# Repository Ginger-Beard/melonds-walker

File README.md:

# melonDS-walker

A DIY USB-C dongle that lets Pokemon HeartGold/SoulSilver running in an emulator talk to a real Pokewalker. An ESP32-S3 and a Vishay TFBS4711 IrDA transceiver act as the IR link, with plug-and-play use after flashing.

This is a personal/community project, not a product. The goal is to upstream IR support into [melonDS Android](https://github.com/rafaelvcaetano/melonDS-android) (rafaelvcaetano/melonDS-android), or failing that to ship it in a fork.

## WARNING: destructive walker commands

Commands 0x2A and 0x2C make the walker wipe itself (pairing, walk, inventory, and for 0x2A lifetime steps), even though 0x2A also replies with the device ID. 0xF0 (factory setup), 0xFE (motion-test setup) and all write commands (EEPROM and RAM writes, walk start/end/update, gift and event commands) are also destructive. `walkerctl` never sends them: a hard-coded allowlist in its send path permits only 0xFA, 0x20, 0x24 and 0xF4 (plus 0x0C reads of exactly 3 payload bytes). Do not bypass this, and take care with any other tool pointed at a real walker.

## Status

Built, tested and working: as of 2026-11-17 the dongle is in regular use, playing HeartGold/SoulSilver in melonDS Android on an AYN Thor with a real Pokéwalker.

First hardware test, 2026-11-12: the XIAO IrDA hat v0.1 worked on first power-on with no rework, and the firmware with default settings talks to a real Pokéwalker. `tools/walkerctl.py handshake` succeeds, and `sniff`, `identify` and `ping` work. On an AYN Thor, the melonDS-android fork (branch `pokewalker-ir`, debug build) used the dongle over USB: HeartGold/SoulSilver erased the walker's old pairing, registered it, and sent a Pokémon on a stroll.

Not tested: the DevKitC-1 build, the TFDU4101 alternate, the melonDS release (R8) build, and measured link range.

## Repo layout

- `docs/research/` research report and notes (protocol, hardware, emulator landscape, Android transport)
  - `report.md` main research report
  - `notes/` raw research notes (e.g. `notes/ir_hardware_and_protocol.md`)
  - `watermelonds-ir-transport.md` analysis of WatermelonDS's IR transport
  - `walker-protocol-facts.md` handshake, checksum, timing and command facts resolved from the walker and HGSS decompilations, plus the walkerctl review
- `docs/protocol.md` host to dongle USB serial protocol
- `docs/hardware.md` DIY build guide and wiring
- `firmware/` ESP32-S3 firmware
- `hardware/xiao-irda-hat/` XIAO ESP32S3 + TFBS4711 hat PCB (tscircuit source, KiCad board, JLCPCB fab files)
- `tools/` `walkerctl.py` bench tool and its tests

## How it works

The IR transceiver is in the game cartridge, not the console. The cart has a small MCU on the cartridge SPI bus that forwards IR packets. melonDS emulates that cart, and sends and receives the IR packets as bytes. The dongle is a byte pipe: it does the IrDA SIR encoding and timing, strips its own echo, splits packets on line idle, and carries them over USB. It does not interpret packet contents. XOR 0xAA, checksums and session IDs are the game's job. See [docs/protocol.md](docs/protocol.md).

## Quick start

1. Build the hardware: [docs/hardware.md](docs/hardware.md).
2. Flash the firmware: `firmware/README.md`.
3. Install the host tool and check the dongle:

```
pip install -r tools/requirements.txt
python3 tools/walkerctl.py identify
python3 tools/walkerctl.py ping -n 50
```

## Test plan

Bench-test against a real walker before touching melonDS: `walkerctl.py sniff` to confirm the 0xFC beacon, then `walkerctl.py handshake` to connect and read the identity. The staged plan is in the "Validating the link without a working DS" section of [docs/research/report.md](docs/research/report.md). The tool never writes to the walker. A read-only EEPROM `dump` is a TODO.

## Prior art and credits

- Dmitry Grinberg, Pokewalker hacking: https://dmitry.gr/?r=05.Projects&proj=28.%20pokewalker
- GBATEK (Martin Korth / nocash), DS Cart Infrared chapter: https://mgba-emu.github.io/gbatek/#dscartinfraredpedometers
- PoroCYon, pokewalker-rom-dumper: https://zff.dev/PoroCYon/pokewalker-rom-dumper
- mamba2410/picowalker: https://github.com/mamba2410/picowalker
- lumirth/pw: https://github.com/lumirth/pw
- lumirth/stickwalker: https://github.com/lumirth/stickwalker
- Flipwalker and FlippIR-Hardware (Jackv-makes): https://github.com/Jackv-makes/Flipwalker, https://github.com/Jackv-makes/FlippIR-Hardware
- WatermelonDS Pokewalker branch (silver115): https://github.com/silver115/WatermelonDS
- DaveuRrr/melonDS-IR: https://github.com/DaveuRrr/melonDS-IR
- melonDS PR #2776: https://github.com/melonDS-emu/melonDS/pull/2776
- PocketWalker (h4lfheart): https://github.com/h4lfheart/PocketWalker
- usb-serial-for-android (mik3y): https://github.com/mik3y/usb-serial-for-android

## Legal

No Nintendo code or data is in this repo. The dongle never needs a ROM; you only need your own game to use it from an emulator.

## License

melonds-walker: IrDA dongle firmware, host tools and hardware for the Pokéwalker.
Copyright (C) 2026 Josh Racine

This program is free software: you can redistribute it and/or modify it under
the terms of the GNU General Public License as published by the Free Software
Foundation, version 3. It is distributed in the hope that it will be useful,
but WITHOUT ANY WARRANTY; without even the implied warranty of MERCHANTABILITY
or FITNESS FOR A PARTICULAR PURPOSE. The full text is in [LICENSE](LICENSE).

This covers the firmware, tools, documents and the hat design files written
for this project. Third-party part models under `hardware/` keep their own terms.

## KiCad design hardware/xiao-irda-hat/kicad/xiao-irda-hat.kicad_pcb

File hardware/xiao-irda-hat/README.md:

# XIAO IrDA hat (v0.1)

A 17.8 x 24.4 mm, 2-layer carrier for a Seeed Studio XIAO ESP32S3 that holds a Vishay TFBS4711 IrDA SIR transceiver. It is the recommended way to build the melonDS-walker dongle. The XIAO sits on top on two 1x7 headers. The transceiver looks out of the end opposite the XIAO's USB-C connector, so with the dongle plugged into a handheld you aim the Pokéwalker at the far end.

Status: built and tested. Two assembled boards ordered from JLCPCB on 2026-11-07 worked on first power-on with no rework (verified 2026-11-12). The firmware with default settings received the walker's beacon and transmitted correctly, and the board is in regular use with the melonDS-android fork and a real Pokéwalker (2026-11-17). Link range has not been measured. Read the [pre-order checklist](#pre-order-checklist-human-checks) before you pay for a reorder.

| Top (XIAO side) | Bottom (outside face) | 3D, factory-assembled |
|---|---|---|
|  |  |  |

Schematic: [renders/schematic.png](renders/schematic.png). 3D views: [renders/3d-top.png](renders/3d-top.png) and [renders/3d-bottom.png](renders/3d-bottom.png). The 3D renders hide the headers because they are marked do-not-populate; `board.step` includes them.

## Design summary

- **Stacking: the hat sits under the XIAO.**
  - The XIAO's BOOT and RESET buttons, its LEDs and the USB-C receptacle are all on its top side, so a hat on top would bury the buttons you need to recover a bad flash.
  - The XIAO's underside has only flat pads: 8 test pads (JTAG/EN/USB) near the USB end, the BAT+/BAT- pads and a logo (Seeed's board file shows no bottom-side parts).
  - Standard male headers leave a 2.54 mm gap (the header plastic) between the hat and the XIAO. That clears the 0603 parts (0.45 to 0.8 mm tall) under the XIAO's far end.
- **IR edge.**
  - The TFBS4711-TR1 is side-view. Its lens tips sit 0.1 mm inside the board edge at the end opposite USB-C, with the whole body inside the outline.
  - The hat runs 3.3 mm past the XIAO's far edge, so the package (back face about 0.2 mm beyond the XIAO edge: 10.80 mm against the XIAO's far edge at 10.594 mm from the header centre) is fully outside the XIAO's shadow and nothing is above it. The rear 0.2 mm of U1's pads does sit under the XIAO edge, so inspect U1's joints before soldering the headers.
  - The pads are 2.2 mm from the edge, so copper stays well over 0.3 mm from the edge everywhere; the optical part needed no exception.
- **Keep-out under the battery pads.** No top copper sits under the XIAO's BAT+/BAT- pads (plus 0.5 mm margin), so a wire soldered there later cannot short anything on the hat. The keep-out runs east to just short of the J1 pads so it leaves no thin sliver of pour.
- **Routing: everything is explicit, no autorouter.**
  - TXD, RXD and SD leave their pads from the inner end, under the package body between the pads and the lenses, and exit east.
  - That nests them in the same order as the XIAO's D0, D1 and D3 pins, so the three signals need no crossings and no vias.
  - Power (VCC2, VCC1, GND) leaves the outer pad ends. The bottom layer is an unbroken GND plane apart from vias.
- **Board:** 2 layers, 1.6 mm FR-4, 1 oz, lead-free HASL, GND pour on both layers, 13 tented GND vias. HASL is fine at 0.95 mm pitch; ENIG would buy nothing but cost. 1.6 mm (not 1.0 mm) because the dongle hangs off a USB port.
  - Rules (JLCPCB 2-layer capability with margin): 0.2 mm clearance and minimum track (signals 0.25 mm, power 0.3 to 0.4 mm), 0.3 mm via drill / 0.6 mm pad, 0.3 mm copper to edge (pours 0.5 mm), silkscreen at least 0.15 mm strokes and 1.0 mm text (JLCPCB minimums), at least 0.3 mm from the outline.

### Circuit and part values

The circuit is Vishay's recommended circuit (datasheet Fig. 1 / Table 1). FlippIR uses the same topology and values.

| Ref | Value | Why |
|---|---|---|
| U1 | TFBS4711-TR1 | Side-view taping, same part as FlippIR/Flipwalker. Alternate: TFBS4711-TR3 (C3171514), also side-view. |
| C1 | 10 µF 10 V X5R 0603 | Datasheet C1: buffers the IRED supply at VCC2 (pin 1) for the up to 430 mA LED pulses; "tantalum or other fast capacitor", and ceramic qualifies. 10 µF rather than 4.7 µF because DC bias at 3.3 V leaves only part of the nominal value (see REVIEW.md, NIT 3). |
| C2 | 100 nF 50 V X7R 0603 | Datasheet C2: VCC1 (pin 5) decoupling, placed right at the pins as the datasheet insists. |
| R2 | 47 Ω 0603 | Datasheet R2: with C2 forms the VCC1 low-pass filter. Drop is under 0.1 V at the 2 mA worst-case dynamic current. |
| (R1) | not fitted | Datasheet R1 is optional and only reduces LED intensity. The TFBS4711 regulates its own IRED current (200 to 430 mA) with no resistor, and we want full range. VCC2 goes straight to 3V3, as on FlippIR. |
| R3 | 10 kΩ 0603, TXD to GND | Keeps the LED dark while GPIO1 floats (reset, ROM bootloader, before the firmware runs). Value below. |
| R4 | 10 kΩ 0603, SD to GND | SD default. See below. |

- **Why 10 k, not FlippIR's 100 k.**
  - The datasheet allows up to 10 µA input leakage on TXD and SD, and only guarantees a low input below 0.4 V.
  - 100 kΩ x 10 µA = 1 V, which is not a guaranteed low; 10 kΩ gives 0.1 V or less.
  - The ESP32-S3 has no internal pull on GPIO1, 2 or 4 at reset (S3 datasheet Table 2-1), so the external resistor alone sets the level.
  - The cost is 0.33 mA while a pin is driven high: during the 1.6 µs TX pulses, or while the host has shut the transceiver down. That doesn't matter for a USB-powered dongle.
- **Why SD is pulled down (transceiver enabled by default).**
  - It matches the firmware. `config.h` defaults `IR_PIN_SD` to GPIO4, and `ir_uart.cpp` drives SD low (enabled) as part of init; it only raises SD when the host sends the disable command. It also matches `-DIR_PIN_SD=-1` builds and other firmware that never touches SD.
  - The datasheet says SD must be grounded for normal operation.
  - It is safe at boot: with SD low the receiver is simply on and drives RXD into GPIO2, an input and not a strapping pin. The LED cannot fire because R3 holds TXD low. Even a stuck-high TXD is cut off by the chip's 100 µs TXD protection.
  - A pull-up would only save the transceiver's 70 µA idle current during boot.

## Pinout

| XIAO pin | XIAO name | ESP32-S3 | Hat net | TFBS4711 pin | Firmware |
|---|---|---|---|---|---|
| 1 (J1.1, square pad) | D0 | GPIO1 | TXD | 2 TXD | `IR_PIN_TX 1` |
| 2 (J1.2) | D1 | GPIO2 | RXD | 3 RXD | `IR_PIN_RX 2` |
| 4 (J1.4) | D3 | GPIO4 | SD | 4 SD | `IR_PIN_SD 4` |
| 12 (J2.5) | 3V3 | 3V3 out | V3V3 | 1 VCC2 (IRED anode), and 5 VCC1 via R2 | |
| 13 (J2.6) | GND | GND | GND | 6 GND | |
| 3, 5, 6, 7, 8, 9, 10, 11, 14 | D2, D4 to D10, 5V | | not connected (holes only, for mechanical strength) | | |

The firmware defaults need no change: `pio run -e seeed_xiao_esp32s3`.

## BOM

Factory-assembled parts, one hat. Library type, stock and price are from JLCPCB's part pages, queried 2026-11-06. Stock moves, so re-check before ordering.

| Ref | Comment | Footprint | LCSC | JLCPCB library | Stock | Unit price (1+) |
|---|---|---|---|---|---|---|
| U1 | TFBS4711-TR1 | TFBS4711 side view | [C102624](https://jlcpcb.com/partdetail/C102624) | **Extended** | 40 | $6.98 |
| (U1 alt) | TFBS4711-TR3 | same | [C3171514](https://jlcpcb.com/partdetail/C3171514) | Extended | 47 | $6.60 |
| C1 | 10 µF 10 V X5R (Samsung CL10A106KP8NNNC) | 0603 | C19702 | Basic | in stock at review (re-check) | re-check |
| C2 | 100 nF 50 V X7R (Yageo CC0603KRX7R9BB104) | 0603 | C14663 | Basic | 34.7 M | $0.009 |
| R2 | 47 Ω 1 % (UniOhm 0603WAF470JT5E) | 0603 | C23182 | Basic | 1.4 M | $0.002 |
| R3, R4 | 10 kΩ 1 % (UniOhm 0603WAF1002T5E) | 0603 | C25804 | Basic | 42.8 M | $0.002 |

Not assembled, hand-soldered by you: J1 and J2, two 1x7 2.54 mm male pin headers (standard 2.54 mm plastic, 6 mm/3 mm pins; often supplied with the XIAO). They are excluded from `fab/bom.csv` and `fab/cpl.csv` (KiCad "exclude from BOM/position files" plus DNP).

### Estimated JLCPCB cost (5 assembled boards, Economic PCBA)

| Item | Estimate |
|---|---|
| 5 PCBs, 2-layer, 1.6 mm, HASL, green | about $2 to 4 |
| PCBA setup + stencil | $8.18 + $1.53 |
| Extended feeder loading (TFBS4711 only; all passives are Basic) | $1.50 to 3.07 (sources disagree; the live quote decides) |
| SMT joints (16 per board) and confirm-placement | about $1.90 |
| Parts: 5 x TFBS4711 at about $6.98, plus passives under $0.50 | about $35.40 |
| **Subtotal before shipping and duty** | **about $50 to 55** |
| Shipping (DHL/FedEx/UPS) plus US import duty | about $20 to 40 (unverified, varies) |

Landed: roughly $70 to 95. The TFBS4711 is now about twice the price the earlier research assumed (it found $3.21). To save about $21, assemble only 2 of the 5 boards; Economic PCBA allows an assembly quantity of 2. Fees are from JLCPCB's price page as recorded in `projects/radio/reports/PCB design tools and fab houses.md`. Prices are not from a live quote.

## Footprint check: datasheet vs LCSC import vs this board

The TFBS4711 footprint is drawn in `index.circuit.tsx` from the datasheet (Vishay 82633 rev. 3.9, Fig. 3 and Fig. 4 "side view application"). `easyeda2kicad --lcsc_id C102624 --full` was used as a cross-check; its output is kept in `footprints/` (LCSC/EasyEDA footprints are not CC-BY-SA).

| Check | Datasheet (side view) | EasyEDA C102624 import | This board |
|---|---|---|---|
| Pads | 6 | 6 | 6 |
| Pitch | 0.95 mm (5 x 0.95 = 4.75) | 0.95 (one gap 0.96 from rounding) | 0.95 |
| Pad size | 0.64 x 1.27 mm | 0.64 x 1.524 mm | 0.64 x 1.27 mm |
| Pad position vs body | pads stick out 0.4 mm behind the back face | 0.50 mm (pad centre 0.26 in front of the back face) | 0.4 mm (pad centre 0.235 in front) |
| Pin order (seen from top, lenses toward you) | 1 VCC2 at left (emitter side) ... 6 GND at right | pin 1 at -X, emitter arc on the pin-1 side | same frame as EasyEDA; placed at 180°, so pin 1 is at +X with the lenses toward the IR edge |
| Optical face | lenses on the side opposite the pads, 3.0 mm from the back face | courtyard to +2.74 mm from pad centre | lens tips 2.765 mm from pad centre, 0.1 mm inside the board edge |
| Body | 6 x 3 x 1.9 mm (±0.2) | courtyard 6 x 3 mm | courtyard 6.5 x 3.6 mm, clipped at the edge |
| 3D model | | STEP is the right shape but half sunk (z ±0.95) and 0.665 mm too far back | offset corrected to (0, -0.665, +0.95) mm; `board.step` places the body at the datasheet position |

Verdict: the EasyEDA footprint is the side-view land pattern with correct pin order and orientation. It differs only in pad length (+0.25 mm), which is harmless. This board uses the datasheet's exact pad, and keeps the EasyEDA orientation so the JLCPCB rotation is just the board rotation (180°). `verify_netlist.py` re-checks U1 on the fab board: 6 pads of 0.64 x 1.27 mm, 0.95 mm pitch, pin 1 at the expected end, and lens tips 0 to 0.3 mm inside the IR edge (actual 0.10 mm).

Other footprints:
- **0603 R/C:** tscircuit's built-in `0603` is two 0.8 x 0.95 mm pads at ±0.825 mm. That is identical to KiCad's `R_0603_1608Metric` / `C_0603_1608Metric` (IPC-7351 nominal).
- **Headers:** drawn in `index.circuit.tsx` as plated holes, 1.0 mm drill and 1.7 mm pad, the same land as KiCad's `PinHeader_1x07_P2.54mm_Vertical`. Seeed's carrier footprint uses 0.889/1.524 mm; 1.0 mm is easier to hand-solder and still holds a 0.64 mm square pin.

## Dimension sources

| Dimension | Value | Source |
|---|---|---|
| XIAO header rows | 2 x 7 holes, 2.54 mm pitch, rows **15.24 mm** apart (x = ±7.62 from centre), pin 1 = D0 at the USB end | Seeed [OPL_Kicad_Library](https://github.com/Seeed-Studio/OPL_Kicad_Library/tree/master/Seeed%20Studio%20XIAO%20Series%20Library), `XIAO-ESP32-S3-DIP.kicad_mod` (pads at ±7.62, ±7.62), and the castellated-pad positions in `Seeed Studio XIAO ESP32S3/ESP32S3.kicad_pcb`. Dimensions only; no Seeed (CC-BY-SA) files are in this repo. The 17.78 mm spacing quoted in the earlier research is wrong. |
| XIAO pin map | D0 = GPIO1, D1 = GPIO2, D3 = GPIO4, pin 12 = 3V3, 13 = GND, 14 = 5V | [Seeed wiki, XIAO ESP32S3 pin map](https://wiki.seeedstudio.com/xiao_esp32s3_getting_started/); OPL symbol `XIAO-ESP32-S3-SMD` (12 3V3_OUT, 13 GND, 14 VBUS) |
| XIAO outline | 17.78 x 21.0 mm; edges at about -10.55 (USB end) and +10.6 (far end) from the header-field centre; USB-C overhangs about 1.5 mm | Seeed wiki spec (21 x 17.8 mm); `XIAO-ESP32-S3-DIP.kicad_mod` courtyard (x -10.425..10.55); `ESP32S3.kicad_pcb` Edge.Cuts |
| XIAO bottom pads | BAT+ (-0.381) and BAT- (-2.286) at 4.445 mm toward the D0 side, 2.03 x 1.02 mm; 8 test pads at ±1.27 mm, -8.64 to -1.02 mm (USB end) | `ESP32S3.kicad_pcb` bottom footprints BAT0, GND0, TP1 to TP8; `XIAO-ESP32-S3-SMD.kicad_mod` pads 15 to 25 |
| Hat outline | 17.8 x 24.4 mm, x ±8.9, y -10.5 (USB end, flush with the XIAO) to +13.9, 1 mm corner radius | derived from the rows above |
| TFBS4711 land pattern | see footprint check | [Vishay TFBS4711 datasheet 82633 rev. 3.9](https://www.vishay.com/docs/82633/tfbs4711.pdf), Fig. 3 and Fig. 4 |
| TFBS4711 circuit | C1 4.7 µF (this board uses 10 µF for DC-bias margin), C2 100 nF, R2 47 Ω, R1 optional; TXD protection 100 µs; input leakage ≤10 µA; VIL ≤0.4 V | same datasheet: Fig. 1, Table 1, pin table, electrical characteristics |
| ESP32-S3 reset state | GPIO1 and GPIO2 input with no pull, GPIO4 disabled with no pull; 60 µs low glitch at power-up | [Espressif ESP32-S3 datasheet v2.2](https://www.espressif.com/sites/default/files/documentation/esp32-s3_datasheet_en.pdf), Tables 2-1 and 2-2 |

### Heights, for the enclosure (`board.step`)

- Hat PCB 1.6 mm, parts on top only.
- Header plastic: 2.54 mm (measured about 2.55 mm on the headers supplied with the XIAO; the 1.9 mm TFBS4711 clears it with room to spare on the v0.1 build), so the XIAO's underside sits **4.14 mm** above the hat's bottom face. Header pins stick out about 3 mm below the hat; trim them flush.
- TFBS4711: 1.9 mm tall. Lens axis 0.95 mm above the hat's top face (2.55 mm above its bottom face), centred on x = 0. Lens tips at y = 13.8 mm, board edge at 13.9 mm.
- Enclosure IR window: at least 6 x 2.5 mm, centred on the lens axis. Half-intensity angle is ±24°.
- `board.step` holds the hat, its SMD parts and both headers. It does not include the XIAO; add Seeed's model on the header plastic at z = 4.14 mm.

## Verification

- **DRC:** `kicad-cli pcb drc --refill-zones`, with the JLCPCB rules above: **0 errors, 0 warnings, 0 unconnected** ([renders/drc-report.txt](renders/drc-report.txt)).
  - Waived: only `lib_footprint_issues` and `lib_footprint_mismatch` are set to ignore in `kicad/xiao-irda-hat.kicad_pro`. These footprints are generated, not taken from a KiCad library, so the library-link checks do not apply.
- **Fab package (independent of the exporters):** `scripts/gerber_netcheck.py` reads `fab/gerbers.zip`, rasterizes both copper layers, joins them through the plated holes and asserts the intended nets by physical pad location, the J1/J2 header geometry (15.24 mm rows, 2.54 mm pitch, D0 = J1.1 at the USB end, 3V3 = J2.5, GND = J2.6, 5V = J2.7 unconnected), and the BOM/CPL (LCSC numbers, U1 at 180°, headers excluded). `scripts/silk_check.py` checks silkscreen strokes (>= 0.15 mm), text height (>= 1.0 mm), silk over pads and silk clearance to the outline (>= 0.3 mm). Both run through `pcb-env/bin/py`; `gerber_netcheck.py --self-test` shows they fail on deliberately broken copies.
- **Netlist:** `python3 verify_netlist.py` checks all 30 pins of the 8 parts against an explicit net table, in both tscircuit's `circuit.json` and the fab KiCad board. It also checks that `firmware/src/config.h`'s GPIO defaults land on the header pins the table says, and checks U1's land pattern and its distance to the IR edge. It passes, and it was checked to fail on a swapped resistor, a moved pad net and a changed firmware pin.

## How to rebuild

Everything runs from the host through the wrappers in `bin/` of the pcb-env distrobox environment (`~/projects/radio/pcb-env`, see its README); a bare `tsci` will not work.

```sh
PCB_ENV=~/projects/radio/pcb-env hardware/xiao-irda-hat/scripts/build.sh
```

| Step | Tool | Output |
|---|---|---|
| 1 | `tsci build` / `tsci export` of `index.circuit.tsx` | `dist/index/circuit.json`, `build/export.kicad_pcb`, `build/export.kicad_sch` |
| 2 | `scripts/kicad_postprocess.py` (KiCad 10 pcbnew) | `kicad/xiao-irda-hat.kicad_{pcb,pro,sch}` |
| 3 | `kicad-cli pcb drc` | `renders/drc-report.txt` (fails the build on any error) |
| 4 | `verify_netlist.py` | pass/fail |
| 5 | `kicad-cli pcb export svg` / `pcb render`, `rsvg-convert` | `renders/*.png` |
| 6 | `kikit fab jlcpcb --assembly --field LCSC --missingError` | `fab/gerbers.zip`, `fab/bom.csv`, `fab/cpl.csv` |
| 6b | `scripts/gerber_netcheck.py`, `scripts/silk_check.py` | pass/fail on the packaged `fab/` files |
| 7 | `kicad-cli pcb export step` | `board.step` |

Placement, pads, every trace and via, the silkscreen, the outline and the keep-out all live in `index.circuit.tsx`. The post-processing step adds only what tscircuit's KiCad export does not carry over, and the script header lists each change:
- deletes empty placeholder footprints the exporter emits for named vias;
- solder paste equal to the pad;
- 0.4 mm refdes moved to the fab layer;
- 3D models;
- the GND zones rebuilt as KiCad zones with thermal reliefs, plus a KiCad rule area for the keep-out;
- design rules, title block, and schematic fields for KiKit.

The KiCad board in `kicad/` opens in the KiCad GUI for human review.

## How to order at JLCPCB

Do not order until the [checklist](#pre-order-checklist-human-checks) is done.

1. On jlcpcb.com, **Order now** and upload `fab/gerbers.zip`. Check the detected size (17.8 x 24.4 mm) and 2 layers, and look at the Gerber viewer: the IR edge, the TFBS pads and the bottom text.
2. PCB options:
   - Base material FR-4, 2 layers, **PCB Qty 5**, Product type: industrial/consumer.
   - Delivery format: single PCB. Thickness 1.6 mm. **Colour green.** Economic PCBA is greyed out for some colours (red, for one), and with it greyed out the page falls back to Standard PCBA, which adds edge rails on every side. Silkscreen white.
   - Surface finish **LeadFree HASL** (or HASL with lead). **Not OSP**, which is now JLCPCB's default and also blocks Economic PCBA. Outer copper 1 oz. Via covering: tented.
   - **Mark on PCB: "Remove Mark".** As of November 2026 the page offers only "Remove Mark" or "2D barcode", with no "Specify a location". The board's `JLCJLCJLCJLC` placeholder then prints literally, hidden under the XIAO. The v0.1 boards were ordered this way. (A later rebuild may drop the placeholder.)
   - Enable **"Confirm Production File"** and inspect JLCPCB's panel before production. Reject any rails, tabs, V-scores or tooling holes on the IR edge (the short edge opposite USB-C); rails or tabs on the two long edges are fine.
   - Leave everything else at the default.
3. Turn on **PCB Assembly**:
   - PCBA type **Economic**. Assembly side **Top**. **PCBA Qty 5** (or 2 to save money).
   - Tooling holes: "Added by JLCPCB". Confirm parts placement: **Yes** ($0.45; an engineer checks orientation).
   - Order remark: *"Please keep panel tabs / mouse bites off the edge with the IR transceiver U1 (the short edge opposite the header pin 1 / USB-C end). U1 is a side-view optical part flush with that edge."*
4. **Next:** upload `fab/bom.csv` (BOM) and `fab/cpl.csv` (pick-and-place). There should be 6 placed parts: U1, C1, C2, R2, R3, R4. J1/J2 are not in the files on purpose.
5. Parts matching: confirm each line shows the LCSC number in the BOM, with stock for 5 boards (plus attrition).
   - If C102624 (TFBS4711-TR1) is short, switch U1 to **C3171514** (TFBS4711-TR3, same side-view taping, same footprint).
   - Only U1 should be Extended.
   - Stock: about 40 x TR1 (C102624) at JLCPCB when last checked, so order soon. C3171514 (TR3) is the alternate.
6. **Placement preview: check U1's rotation and position.**
   - **Quick check:** with the IR edge at the top of the preview, the lenses point up (toward the edge) and the pin-1 marker is at the right-hand end of the pad row, next to C1. A 180° error would put 3V3 on the GND pad.
   - The two round lenses must face **outward, flush with the board edge farthest from the USB-C end** (the edge with the "IR" arrows). The flat back with the 6 terminals faces the passives.
   - The terminals must sit on the 6 pads.
   - If the part points into the board, set U1 rotation to 0° in the preview (or add a `JLCPCB_CORRECTION` field `0;0;180` to U1 and rebuild). If it is shifted by about 1.3 mm along the lens axis, JLCPCB's model origin is the body centre rather than the pad row; correct the offset in the preview.
   - Also glance at the five 0603 parts (rotation doesn't matter electrically).
7. Review the quote, then pay. The DDP duty line and shipping method appear at checkout.

## Hand-soldering the headers

1. The XIAO goes on **top** of the hat, component side up, its USB-C at the hat's "USB-C" end (the end with the square pad, J1.1 = D0). The transceiver end sticks out past the XIAO's far edge.
2. Keep the **2.54 mm header plastic between the boards**. Do not mount the XIAO flush: the passives under its far end need the gap.
3. Easiest order:
   - Put the long pins of two 1x7 headers through the XIAO from below (plastic against the XIAO's underside) and solder them on the XIAO's top.
   - Then drop the short pins into the hat from the top and solder them on the hat's bottom face.
   - If your XIAO came with headers already soldered pins-down, use the same procedure from the second step.
4. Solder all 14 pins; the unused ones carry nothing but add strength. Tack two opposite corner pins first and check that the boards are parallel and the XIAO is square to the hat, then do the rest.
5. GND (J2.6) has thermal reliefs on both pour layers, but still needs a bit more heat than the others. Trim the pins flush on the hat's bottom so the dongle sits flat.
6. Before plugging in, check with a meter: 3V3 (J2.5) to GND (J2.6) is not shorted, and TXD (J1.1) to GND reads about 10 kΩ.

## Assumptions

- The XIAO ESP32S3 (non-Sense) is used. The Sense variant's camera board is on top and does not conflict, but was not checked.
- Standard headers with 2.54 mm plastic. Low-profile or machined-pin headers with a smaller gap would put the XIAO onto C1, C2, R2 and R4. The XIAO's USB-C shell legs sit above R3 (leg S2 overlaps R3 pad 1 in XY), which has about 1 mm of vertical clearance with standard headers, so never use low-profile headers.
- The XIAO's 3V3 regulator can supply the TFBS4711's LED pulses: 300 mA typical, 430 mA max, 1.6 µs long, 3/16 duty during a run of zero bits. That averages about 56 mA typical and 81 mA worst case, inside the datasheet's 85 mA limit for pin 1. C1 supplies the peaks locally.
- JLCPCB's internal footprint for C102624 has the same 0° orientation and origin as the EasyEDA footprint. That's why the CPL says 180° at the pad-row centre.
- No silkscreen refdes on the board; designators are on the fab layer and in the renders. There is no room for 1.0 mm refdes next to every part.
- **The XIAO's USB-C is a receptacle.** The dongle exposes a female port, so plugging it into a handheld needs a short male-to-male USB-C cable or adapter. A right-angle or U-shaped M-M adapter is the compact option.

## Open questions

- **Rotation and origin of U1 at JLCPCB:** resolved. JLCPCB placed U1 correctly at 180° and the board works.
- **Stock:** 40 x TR1 and 47 x TR3 at JLCPCB on 2026-11-06. A reorder from this repo may find both gone; Digi-Key/Mouser plus hand or hot-air assembly is the fallback.
- **Panel tabs:** Economic PCBA may ship panelized with mouse bites. A tab on the IR edge would leave a nub of up to about 0.5 mm in front of the lenses (file it off). The order remark asks JLCPCB to avoid it.
- **Signals under the package:** TXD, RXD and SD run under the TFBS4711 body, mostly under the emitter half; the detector half only has the start of the SD stub. Vishay's layout note asks only for short, low-inductance supply wiring, and none of these is a supply. I expect no effect but it is untested.
- **Firmware comment (fixed):** `config.h`, `firmware/README.md` and `docs/hardware.md` now give the TFBS4711 TXD watchdog as 100 µs (the TFDU4101's is 50 µs).

## Pre-order checklist (human checks)

1. Open `kicad/xiao-irda-hat.kicad_pcb` in the KiCad GUI once. Look at the TFBS4711: lenses at the edge, pin 1 (dot) next to C1.
2. Compare the TFBS4711 pads against datasheet Fig. 4 yourself (0.95 mm pitch, 0.64 x 1.27 mm, 0.4 mm behind the back face).
3. Hold a XIAO against `renders/pcb-top.png` printed at 1:1 (17.8 mm wide), or measure your XIAO: rows 15.24 mm apart, pin 1 at the USB end on the D0 side.
4. Check live stock and Basic/Extended status for all six LCSC numbers.
5. In the JLCPCB placement preview: U1 rotation and position (step 6 above).
6. Read the quote's duty and shipping lines.

## Files

| Path | What |
|---|---|
| `index.circuit.tsx` | the board, in tscircuit |
| `package.json` | project metadata for `tsci` (no npm dependencies; tscircuit comes from pcb-env) |
| `scripts/build.sh` | end-to-end rebuild |
| `scripts/kicad_postprocess.py` | tscircuit KiCad export to fab-ready KiCad board |
| `verify_netlist.py` | pin-by-pin netlist check (exporter data) |
| `scripts/gerber_netcheck.py`, `scripts/silk_check.py`, `scripts/gerblib.py` | gerber-level connectivity, BOM/CPL and silkscreen checks on `fab/` |
| `footprints/` | easyeda2kicad import of C102624 (symbol, footprint, STEP/WRL), the cross-check reference and the 3D model source |
| `kicad/` | generated, fab-ready KiCad board, project (rules) and schematic |
| `fab/` | `gerbers.zip`, `bom.csv`, `cpl.csv` for JLCPCB |
| `renders/` | PCB top/bottom, tscircuit view, schematic, 3D renders, DRC report |
| `board.step` | 3D model of the assembled hat with headers, for the enclosure |

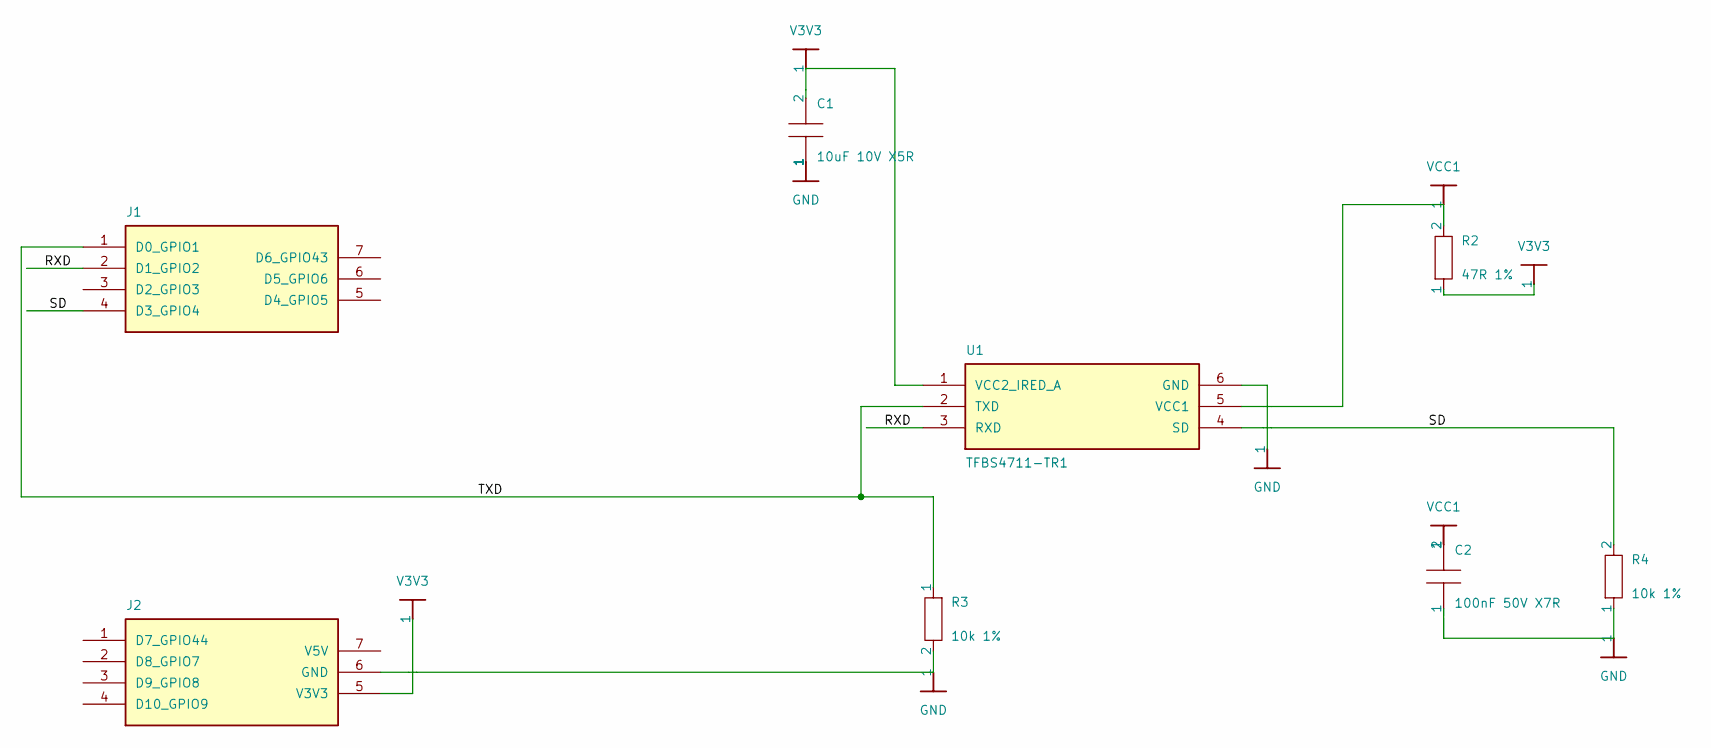
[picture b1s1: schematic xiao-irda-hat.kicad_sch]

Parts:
C1: 10uF 10V X5R; C_0603_1608Metric; LCSC C19702
C2: 100nF 50V X7R; C_0603_1608Metric; LCSC C14663
J1, J2: XIAO_Header_1x07_P2.54mm
R2: 47R 1%; R_0603_1608Metric; LCSC C23182
R3, R4: 10k 1%; R_0603_1608Metric; LCSC C25804
U1: TFBS4711-TR1; TFBS4711_SideView_Vishay; LCSC C102624

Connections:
GND: C1.1, C2.1, J2.6 (GND), R3.2, R4.1, U1.6 (GND)
RXD: J1.2 (D1_GPIO2), U1.3 (RXD)
SD: J1.4 (D3_GPIO4), R4.2, U1.4 (SD)
TXD: J1.1 (D0_GPIO1), R3.1, U1.2 (TXD)
V3V3: C1.2, J2.5 (V3V3), R2.1, U1.1 (VCC2_IRED_A)
VCC1: C2.2, R2.2, U1.5 (VCC1)

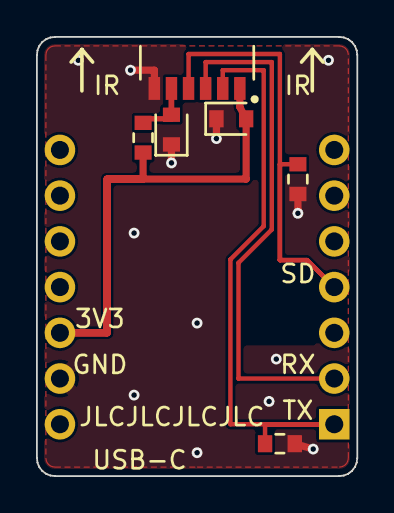
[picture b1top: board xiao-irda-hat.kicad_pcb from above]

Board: 2 copper layers, 17.8 x 24.4 mm, 8 parts (0 on the bottom side), 6 nets.

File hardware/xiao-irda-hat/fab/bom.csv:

Comment,Designator,Footprint,LCSC Part #
TFBS4711-TR1,U1,TFBS4711_SideView_Vishay,C102624
10uF 10V X5R,C1,C_0603_1608Metric,C19702
100nF 50V X7R,C2,C_0603_1608Metric,C14663
47R 1%,R2,R_0603_1608Metric,C23182
10k 1%,"R3,R4",R_0603_1608Metric,C25804
